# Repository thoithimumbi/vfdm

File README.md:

# Vibration Fault Diagnostics in Motors (VFDM)  |  In Progress 

**Background.** Electric motors drive critical equipment like pumps and fans, emitting distinct vibration signatures before mechanical failure. Unplanned breakdowns cause high operational costs and downtime. Existing monitoring relies on manual inspections that miss sudden faults or cloud systems burdened by high latency, bandwidth consumption, and network dependency. This project evaluates an offline Edge-AI solution on a low-cost STM32 microcontroller for real-time motor fault classification without cloud infrastructure.

**Methods.** Conducted at Dedan Kimathi University of Technology, the setup uses a motor test rig simulating shaft unbalance and structural looseness. An ADXL345 accelerometer rigidly mounted to the motor casing streams vibration data via SPI/I2C through a custom KiCad PCB shield to an STM32F411CEU6 MCU. On-chip features (RMS, Kurtosis, Crest Factor, CMSIS-DSP FFT) are processed by an INT8 quantized machine learning model deployed via ST X-CUBE-AI for local inference.

**Results.** The pipeline targets $\ge 90\%$ classification accuracy across healthy, unbalance, and looseness states on the test rig. INT8 quantization enables sub-100 ms execution per cycle within the MCU's memory constraints ($512\text{ KB}$ Flash, $128\text{ KB}$ SRAM), providing $100\%$ offline fault detection without cloud or PC dependency.

**Conclusions.** Low-cost microcontrollers can replace cloud-dependent condition monitoring platforms through localized, real-time vibration diagnostics. Combining direct adhesive sensing, DSP feature extraction, and quantized neural networks eliminates network latency and inspection delays, delivering an accessible predictive maintenance tool for industrial operators.

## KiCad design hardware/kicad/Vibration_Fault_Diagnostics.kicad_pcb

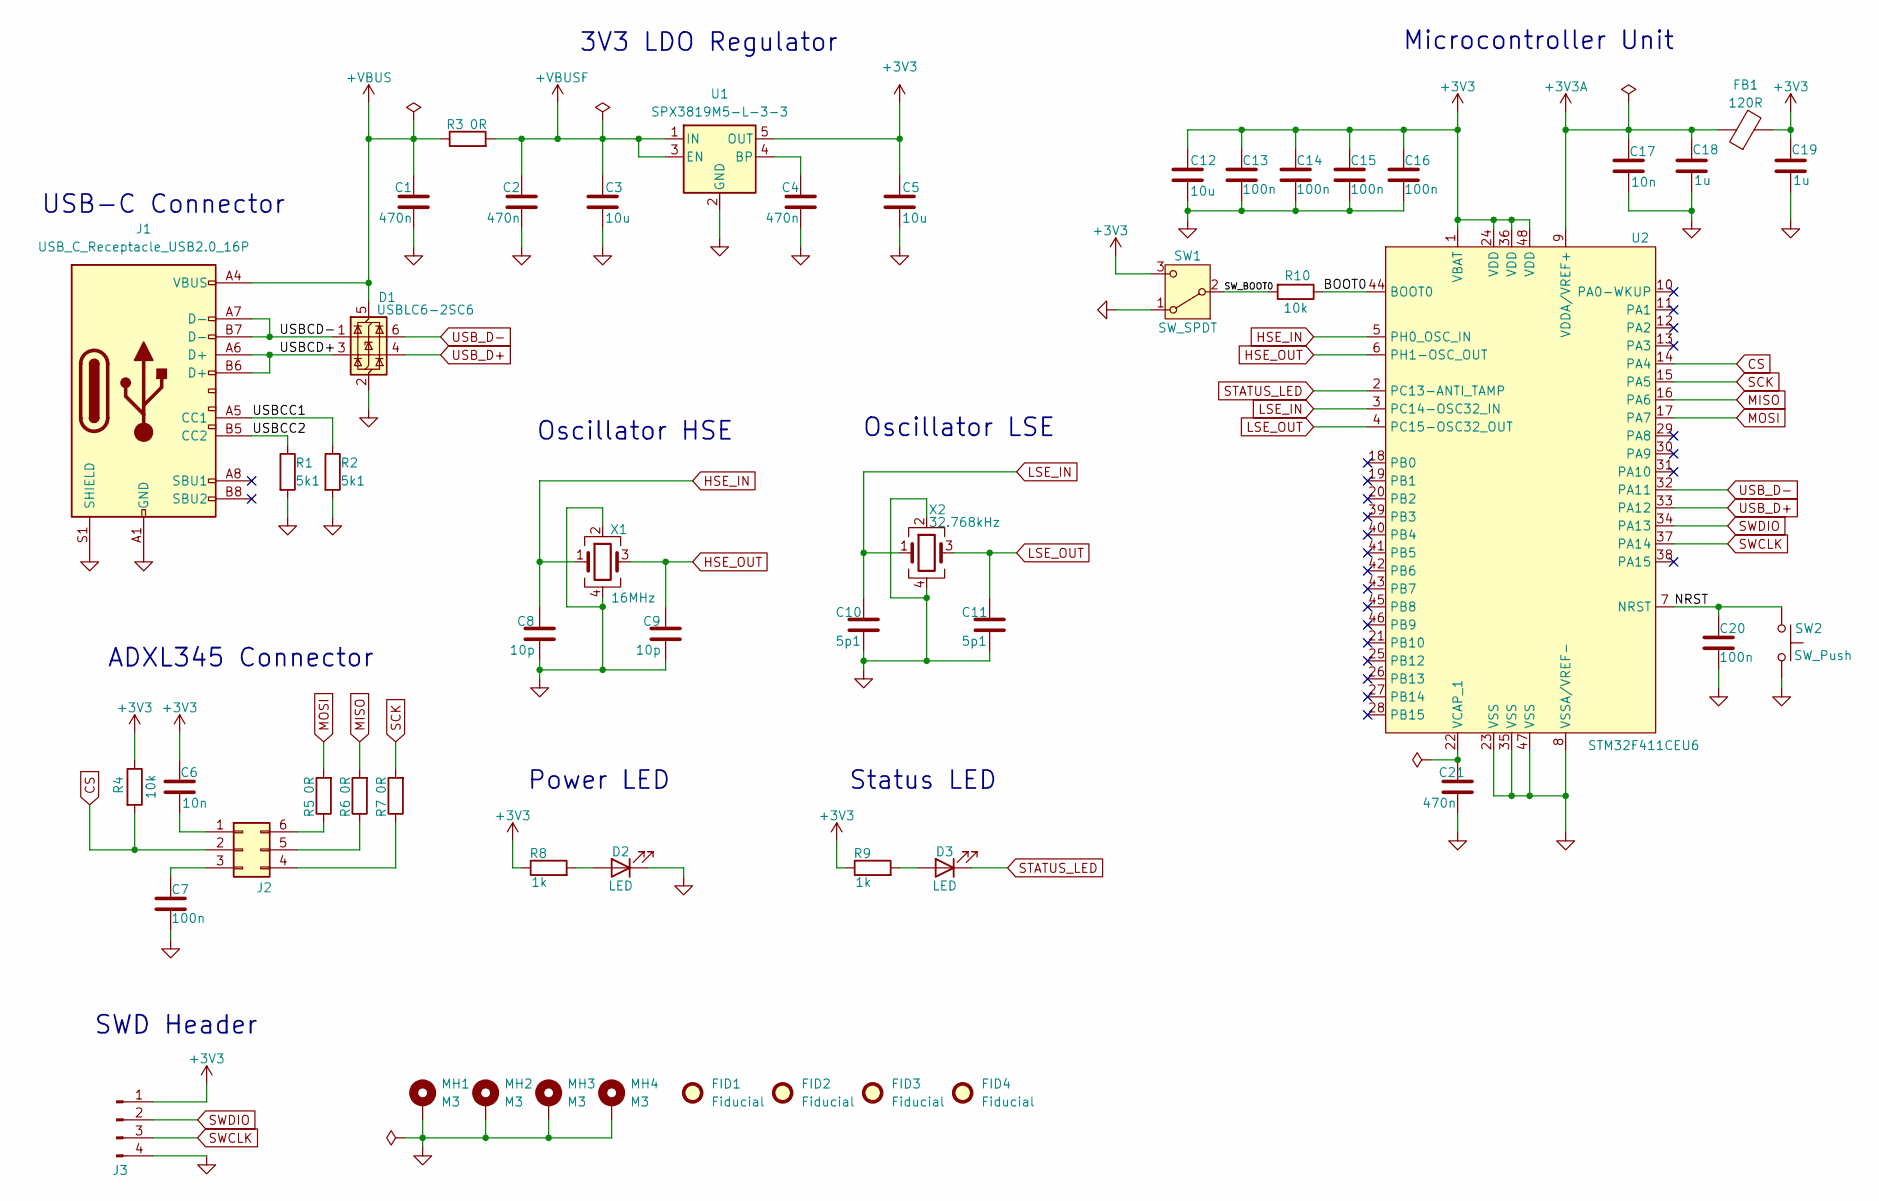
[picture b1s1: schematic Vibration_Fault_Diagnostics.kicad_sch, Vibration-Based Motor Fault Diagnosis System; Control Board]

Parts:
C1, C2, C4, C21: 470n; C_0603_1608Metric; Manufacturer Part Number CL10B474KA8NNNC; LCSC C1623
C3, C5, C12: 10u; C_1206_3216Metric; Manufacturer Part Number CL21B106KQQNNNE; LCSC C100083
C6, C17: 10n; C_0201_0603Metric; Manufacturer Part Number CC0603KRX7R9BB103; LCSC C100042
C7, C13, C14, C15, C16, C20: 100n; C_0603_1608Metric; Manufacturer Part Number CL10B104KB8NNNC; LCSC C1591
C8, C9: 10p; C_0603_1608Metric; Manufactuer Part Number CL10C100JB8NNNC; LCSC C1634
C10, C11: 5p1; C_0603_1608Metric; Manufacturer Part Number CL10C5R1CB8NNNC; LCSC C377765
C18, C19: 1u; C_0603_1608Metric; Manufacturer Part Number CL10B105KO8NNNC; LCSC C59782
D1: USBLC6-2SC6; SOT-23-6; Manufacturer Part Number USBLC6-2SC6; LCSC C7519
D2: LED; LED_0603_1608Metric; Manufacturer Part Number KT-0603R; LCSC C2286
D3: LED; LED_0603_1608Metric; Manufacturer Part Number KT-0603G; LCSC C12624
FB1: 120R; L_Eaton_MCL2012V1; Manufacturer Part Number BLM18KG121TN1D; LCSC C85831
FID1, FID2, FID3, FID4: Fiducial; Fiducial_1mm_Mask2mm
J1: USB_C_Receptacle_USB2.0_16P; USB_C_Receptacle_GCT_USB4105-xx-A_16P_TopMnt_Horizontal; Manufacturer Part Number TYPE-C-31-M-12A; LCSC C5337088
J2: Conn_02x03_Counter_Clockwise; PinHeader_2x03_P2.54mm_Vertical; Manufacturer Part Number 2.54-2*3; LCSC C5116479
J3: Conn_01x04_Pin; PinHeader_1x04_P2.54mm_Horizontal; Manufacturer Part Number A2541WR-4P; LCSC C225490
MH1, MH2, MH3, MH4: M3; MountingHole_3.2mm_M3_Pad_Via
R1, R2: 5k1; R_0603_1608Metric; Manufacturer Part Number 0603WAF5101T5E; LCSC C23186
R3, R5, R6, R7: 0R; R_0603_1608Metric; Manufacturer Part Number 0603WAF0000T5E; LCSC C21189
R4, R10: 10k; R_0603_1608Metric; Manufacturer Part Number 0603WAF1002T5E; LCSC C25804
R8, R9: 1k; R_0603_1608Metric; Manufacturer Part Number 0603WAF1001T5E; LCSC C21190
SW1: SW_SPDT; SW_SPDT_PCM12; Manufacturer Part Number PCM12SMTR; LCSC C221841
SW2: SW_Push; SW_SPST_TL3342; Manufacturer Part Number TS-1088-AR02016; LCSC C720477
U1: SPX3819M5-L-3-3; SOT-23-5; Manufacturer Part Number SPX3819M5-L-3-3/TR; LCSC C9055
U2: STM32F411CEU6; QFN-48-1EP_7x7mm_P0.5mm_EP5.6x5.6mm; Manufacturer Part Number STM32F411CEU6; LCSC C60420
X1: 16MHz; Crystal_SMD_3225-4Pin_3.2x2.5mm; Manufacturer Part Number X322516MLB4SI; LCSC C13738
X2: 32.768kHz; Crystal_SMD_3225-4Pin_3.2x2.5mm; Manufacturer Part Number X321532768KGD4SI; LCSC C620155

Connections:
+3V3: C5.1, C6.1, C12.1, C13.1, C14.1, C15.1, C16.1, C19.1, FB1.2, J3.1, R4.1, R8.1, R9.1, SW1.3 (C), U1.5 (OUT), U2.1 (VBAT), U2.24 (VDD), U2.36 (VDD), U2.48 (VDD)
+3V3A: C17.1, C18.1, FB1.1, U2.9 (VDDA/VREF+)
+VBUS: C1.1, D1.5 (VBUS), J1.A4 (VBUS), J1.A9 (VBUS), J1.B4 (VBUS), J1.B9 (VBUS), R3.1
+VBUSF: C2.1, C3.1, R3.2, U1.1 (IN), U1.3 (EN)
/BOOT0: R10.1, U2.44 (BOOT0)
/NRST: C20.1, SW2.1, U2.7 (NRST)
/SW_BOOT0: R10.2, SW1.2 (B)
/USBCC1: J1.A5 (CC1), R2.1
/USBCC2: J1.B5 (CC2), R1.1
/USBCD+: D1.3 (I/O2), J1.A6 (D+), J1.B6 (D+)
/USBCD-: D1.1 (I/O1), J1.A7 (D-), J1.B7 (D-)
CS: J2.2, R4.2, U2.14 (PA4)
GND: C1.2, C2.2, C3.2, C4.2, C5.2, C7.2, C8.2, C9.2, C10.2, C11.2, C12.2, C13.2, C14.2, C15.2, C16.2, C17.2, C18.2, C19.2, C20.2, C21.2, D1.2 (GND), D2.1 (K), J1.A1 (GND), J1.A12 (GND), J1.B1 (GND), J1.B12 (GND), J1.S1 (SHIELD), J3.4, MH1.1 (1_1), MH2.1 (1_1), MH3.1 (1_1), MH4.1 (1_1), R1.2, R2.2, SW1.1 (A), SW2.2, U1.2 (GND), U2.8 (VSSA/VREF-), U2.23 (VSS), U2.35 (VSS), U2.47 (VSS), X1.2, X1.4, X2.2, X2.4
HSE_IN: C8.1, U2.5 (PH0_OSC_IN), X1.1
HSE_OUT: C9.1, U2.6 (PH1-OSC_OUT), X1.3
LSE_IN: C10.1, U2.3 (PC14-OSC32_IN), X2.1
LSE_OUT: C11.1, U2.4 (PC15-OSC32_OUT), X2.3
MISO: R6.2, U2.16 (PA6)
MOSI: R5.2, U2.17 (PA7)
unnamed: D2.2 (A), R8.2
unnamed: D3.2 (A), R9.2
unnamed: C6.2, J2.1
unnamed: C7.1, J2.3
unnamed: J2.4, R7.1
unnamed: J2.5, R6.1
unnamed: J2.6, R5.1
unnamed: C4.1, U1.4 (BP)
unnamed: C21.1, U2.22 (VCAP_1)
SCK: R7.2, U2.15 (PA5)
STATUS_LED: D3.1 (K), U2.2 (PC13-ANTI_TAMP)
SWCLK: J3.3, U2.37 (PA14)
SWDIO: J3.2, U2.34 (PA13)
USB_D+: D1.4 (I/O2), U2.33 (PA12)
USB_D-: D1.6 (I/O1), U2.32 (PA11)

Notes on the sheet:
3V3 LDO Regulator
Oscillator LSE
Microcontroller Unit
Status LED
Oscillator HSE
ADXL345 Connector
USB-C Connector
Power LED
SWD Header

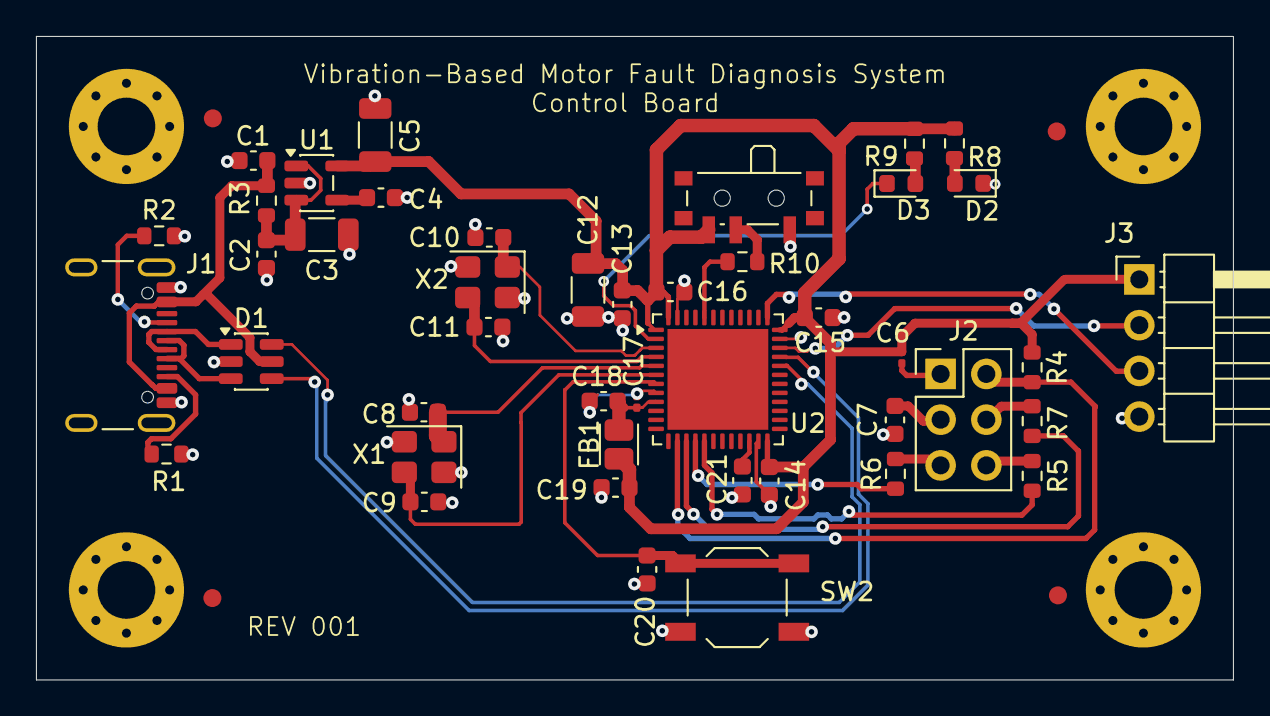
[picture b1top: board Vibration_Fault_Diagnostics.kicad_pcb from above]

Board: 2 copper layers, 66.5 x 35.8 mm, 52 parts (0 on the bottom side), 34 nets.
